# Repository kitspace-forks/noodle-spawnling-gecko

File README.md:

# Noodle Spawnling Gecko Brain

This is a brain for a [noodle spawnling](http://roboticarts.zoness.com/2017/12/19/birthing-a-noodle-spawnling/), a small 3d-printed robot figurine designed by spetku.

</img>

I am building a noodle spawnling for myself and also wanted to learn more about programming ARM Cortex uCs, so I made this brain board to do both at the same time.

## Features
  * Silicon Labs Happy Gecko EFM32HG309 microcontroller (the same one as on the [tomu.im](https://tomu.im))
  * buzzer
  * 2 LEDs
  * capacitive touch button area
  * micro USB connector
  * SWD debug and a combined (LEU/US)ART header
  * CR2032 coincell holder

For the BOM see [doc/bom.csv](doc/bom.csv).

## Additional tools
Besides KiCad, some additional tools were used on this project:
  * For BOM management I used [BOMs Away](https://github.com/Jeff-Ciesielski/Boms-Away)
  * [doc/stickerbom.pdf](doc/stickerbom.pdf) was generated with [StickerBOM](https://github.com/adamgreig/agg-kicad/wiki/StickerBOM)

## License
CC BY-SA 4.0 (https://creativecommons.org/licenses/by-sa/4.0/)

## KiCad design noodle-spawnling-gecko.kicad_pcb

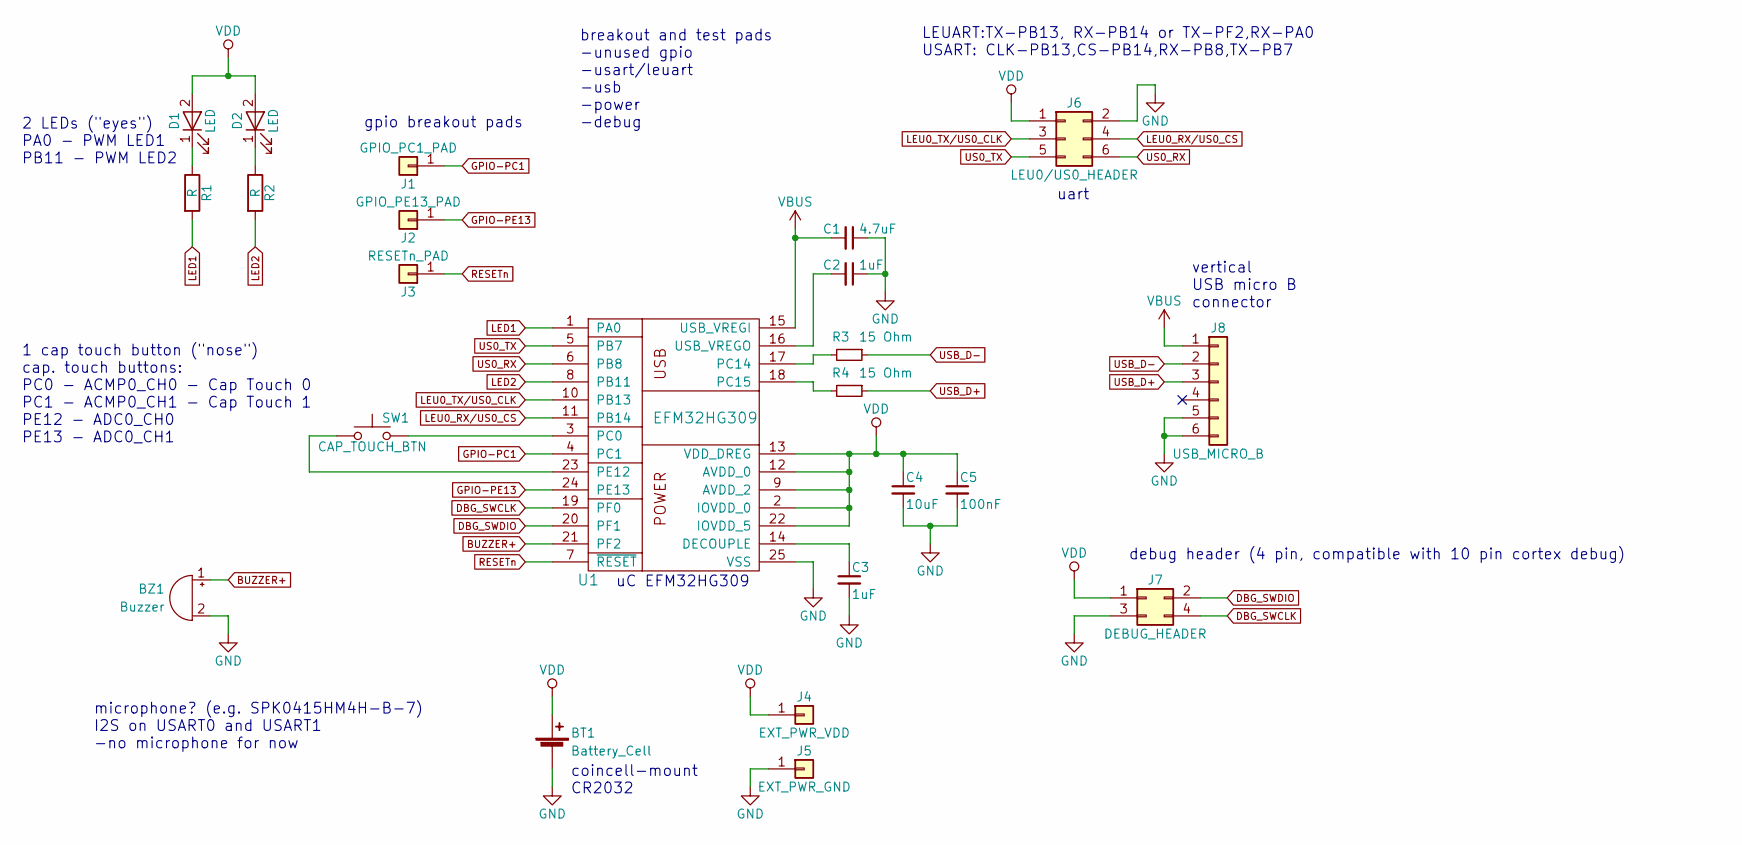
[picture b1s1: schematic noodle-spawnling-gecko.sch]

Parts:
BT1: Battery_Cell; CR2032_holder_smd
BZ1: Buzzer; Buzzer_Murata_PKMCS0909E4000-R1
C1: 4.7uF; C_0402_NoSilk
C2, C3: 1uF; C_0402_NoSilk
C4: 10uF; C_0402_NoSilk
C5: 100nF; C_0402_NoSilk
D1, D2: LED; led_5mm_horizontal_pads
J1: GPIO_PC1_PAD; pcb_pad_single_1,5mm
J2: GPIO_PE13_PAD; pcb_pad_single_1,5mm
J3: RESETn_PAD; pcb_pad_single_1,5mm
J4: EXT_PWR_VDD; Pin_d1.0mm_L10.0mm_noSilk
J5: EXT_PWR_GND; Pin_d1.0mm_L10.0mm_noSilk
J6: LEU0/US0_HEADER; header_smd_0.05pitch_2row_6pin
J7: DEBUG_HEADER; header_smd_0.05pitch_2row_4pin
J8: USB_MICRO_B; usb_microb_smd_vertical
R1, R2: R; R_0402_NoSilk
R3, R4: 15 Ohm; R_0402_NoSilk
SW1: CAP_TOUCH_BTN; cap_touch_pads
U1: EFM32HG309; QFN-24-1EP_5x5mm_Pitch0.65mm

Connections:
BUZZER+: BZ1.1 (-), U1.21 (PF2)
DBG_SWCLK: J7.4, U1.19 (PF0)
DBG_SWDIO: J7.2, U1.20 (PF1)
GND: BT1.2 (-), BZ1.2 (+), C1.1, C2.1, C3.2, C4.2, C5.2, J5.1, J6.2, J7.3, J8.5, J8.6, U1.25 (VSS)
GPIO-PC1: J1.1, U1.4 (PC1)
GPIO-PE13: J2.1, U1.24 (PE13)
LED1: R1.2, U1.1 (PA0)
LED2: R2.2, U1.8 (PB11)
LEU0_RX/US0_CS: J6.4, U1.11 (PB14)
LEU0_TX/US0_CLK: J6.3, U1.10 (PB13)
unnamed: C2.2, U1.16 (USB_VREGO)
unnamed: C3.1, U1.14 (DECOUPLE)
unnamed: D1.1 (K), R1.1
unnamed: D2.1 (K), R2.1
unnamed: R3.2, U1.17 (PC14)
unnamed: R4.2, U1.18 (PC15)
unnamed: SW1.1, U1.23 (PE12)
unnamed: SW1.2, U1.3 (PC0)
RESETn: J3.1, U1.7 (~RESET)
US0_RX: J6.6, U1.6 (PB8)
US0_TX: J6.5, U1.5 (PB7)
USB_D+: J8.3, R4.1
USB_D-: J8.2, R3.1
VBUS: C1.2, J8.1, U1.15 (USB_VREGI)
VDD: BT1.1 (+), C4.1, C5.1, D1.2 (A), D2.2 (A), J4.1, J6.1, J7.1, U1.2 (IOVDD_0), U1.9 (AVDD_2), U1.12 (AVDD_0), U1.13 (VDD_DREG), U1.22 (IOVDD_5)

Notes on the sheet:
uC EFM32HG309
2 LEDs ("eyes") PA0 - PWM LED1 PB11 - PWM LED2
debug header (4 pin, compatible with 10 pin cortex debug)
coincell-mount CR2032
vertical USB micro B connector
breakout and test pads -unused gpio -usart/leuart -usb -power -debug
microphone? (e.g. SPK0415HM4H-B-7) I2S on USART0 and USART1 -no microphone for now
LEUART:TX-PB13, RX-PB14 or TX-PF2,RX-PA0 USART: CLK-PB13,CS-PB14,RX-PB8,TX-PB7
1 cap touch button ("nose") cap. touch buttons: PC0 - ACMP0_CH0 - Cap Touch 0 PC1 - ACMP0_CH1 - Cap Touch 1 PE12 - ADC0_CH0 PE13 - ADC0_CH1
gpio breakout pads
uart

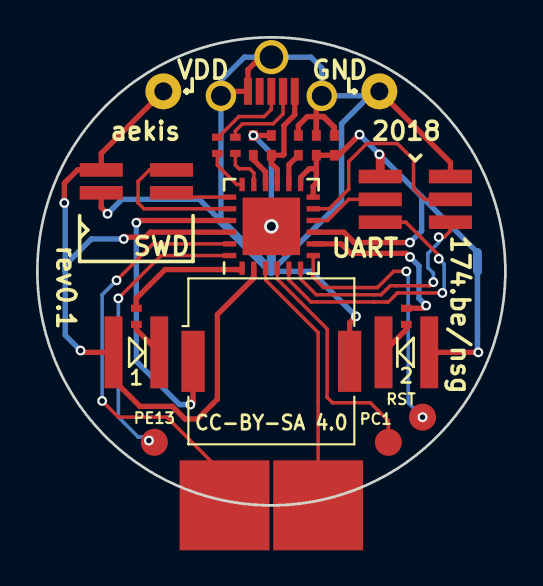
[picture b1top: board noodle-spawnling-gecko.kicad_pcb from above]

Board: 2 copper layers, 26.0 x 26.0 mm, 23 parts (1 on the bottom side), 25 nets.

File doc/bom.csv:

Refs,Value,Footprint,QTY,MFR,MPN,SPR,SPN
BZ1,Buzzer,Buzzers_Beepers:Buzzer_Murata_PKMCS0909E4000-R1,1,Murata Electronics North America,PKMCS0909E4000-R1,Digikey,490-9647-1-ND
C5,100nF,Capacitors_SMD:C_0402_NoSilk,1,Samsung Electro-Mechanics,CL05A104KQ5NNNC,Digikey,1276-1442-1-ND
C4,10uF,Capacitors_SMD:C_0402_NoSilk,1,Murata Electronics North America,GRM155C80J106ME11D,Digikey,490-13233-1-ND
C3;C2,1uF,Capacitors_SMD:C_0402_NoSilk,2,Samsung Electro-Mechanics,CL05X105KQ5NNNC,Digikey,1276-1754-1-ND
C1,4.7uF,Capacitors_SMD:C_0402_NoSilk,1,Samsung Electro-Mechanics,CL05A475KQ5NRNC ,Digikey,1276-1481-1-ND
U1,EFM32HG309,Housings_DFN_QFN:QFN-24-1EP_5x5mm_Pitch0.65mm,1,Silicon Labs ,EFM32HG309F64G-B-QFN24,Digikey,336-3896-ND
R3;R4,15 Ohm,Resistors_SMD:R_0402_NoSilk,2,Panasonic Electronic Components,ERJ-2RKF15R0X,Digikey,P15.0LCT-ND
R1;R2,R,Resistors_SMD:R_0402_NoSilk,2,Yageo,RC0402FR-0752R3L,Digikey,YAG3180CT-ND
BT1,Battery_Cell,coincell_smd:CR2032_holder_smd,1,Linx Technologies Inc. ,BAT-HLD-001,Digikey,BAT-HLD-001-ND
J5,EXT_PWR_GND,headers-tht:Pin_d1.0mm_L10.0mm_noSilk,1,Amphenol FCI,68000-401HLF,Digikey,609-3466-ND
J4,EXT_PWR_VDD,headers-tht:Pin_d1.0mm_L10.0mm_noSilk,1,Amphenol FCI,68000-401HLF,Digikey,609-3466-ND
J7,DEBUG_HEADER,headers_smd:header_smd_0.05pitch_2row_4pin,1,Sullins Connector Solutions,GRPB022VWQS-RC,Digikey,S9012E-02-ND
J6,LEU0/US0_HEADER,headers_smd:header_smd_0.05pitch_2row_6pin,1,Amphenol FCI,20021121-00006C4LF,Digikey,609-3693-1-ND
SW1,CAP_TOUCH_BTN,pcb_pads:cap_touch_pads,1,-,-,-,-
D1;D2,LED,pcb_pads:led_5mm_horizontal_pads,2,Wurth Electronics Inc.,151051SS04000,Digikey,732-11405-ND
J1,GPIO_PC1_PAD,"pcb_pads:pcb_pad_single_1,5mm",1,-,-,-,-
J2,GPIO_PE13_PAD,"pcb_pads:pcb_pad_single_1,5mm",1,-,-,-,-
J3,RESETn_PAD,"pcb_pads:pcb_pad_single_1,5mm",1,-,-,-,-
J8,USB_MICRO_B,usb_smd:usb_microb_smd_vertical,1,"Molex, LLC",1051330011,Digikey,WM10134CT-ND

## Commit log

2018-04-01 initial commit; revision 0.1
2018-04-01 add license to the silkscreen
2018-04-01 add bom
2018-04-02 add stickerbom pdf
2018-04-02 add schematic pdf and board render photos
2018-04-14 add README
2018-04-14 fix image link in README
2018-04-14 Improve README
2018-04-17 add motivation to README

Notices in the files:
noodle-spawnling-gecko.kicad_pcb:
Licence: CC BY-SA 4.0 (https://creativecommons.org/licenses/by-sa/4.0/)
